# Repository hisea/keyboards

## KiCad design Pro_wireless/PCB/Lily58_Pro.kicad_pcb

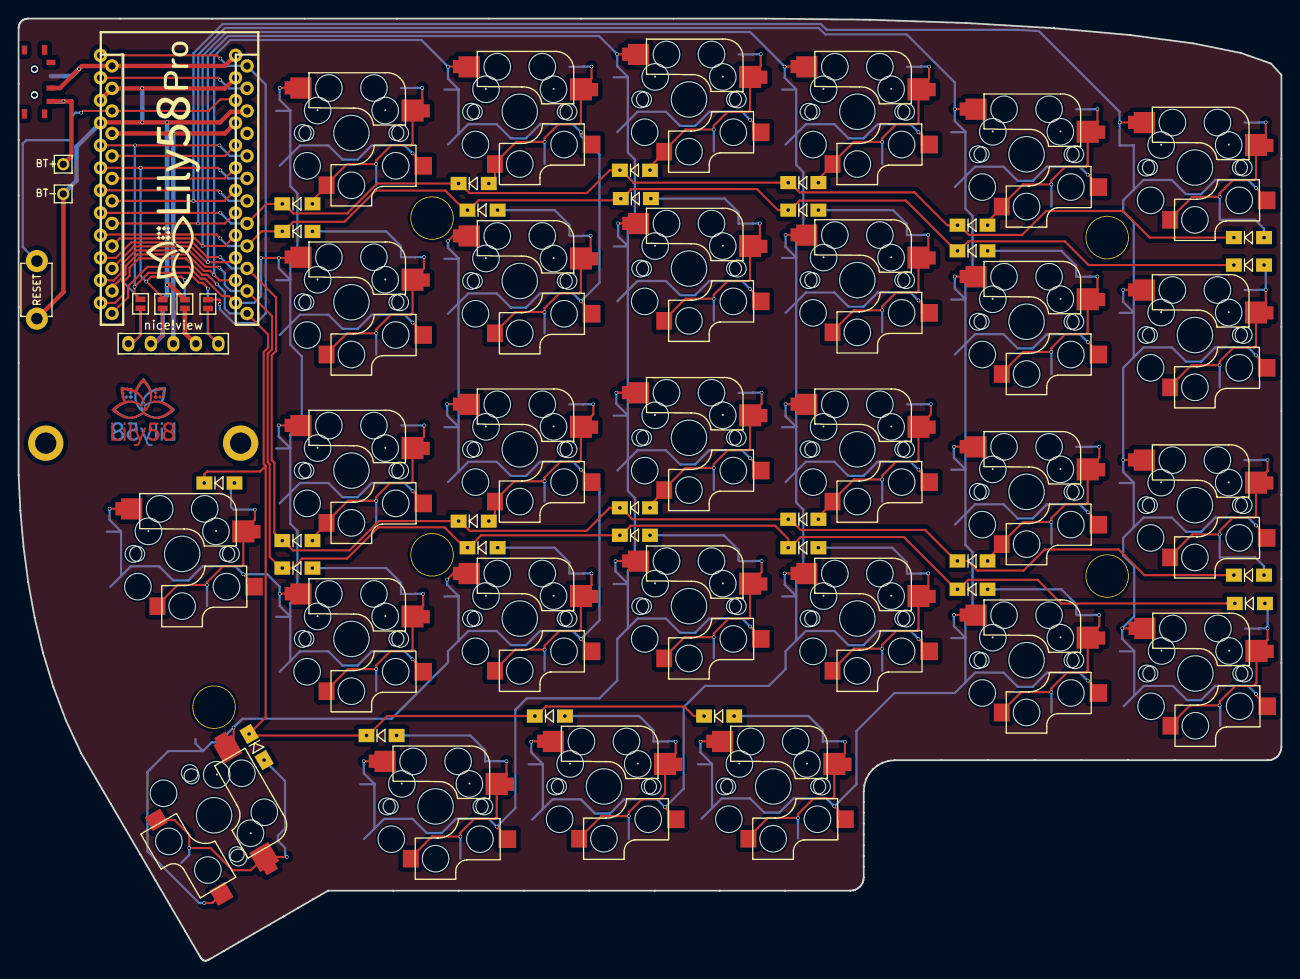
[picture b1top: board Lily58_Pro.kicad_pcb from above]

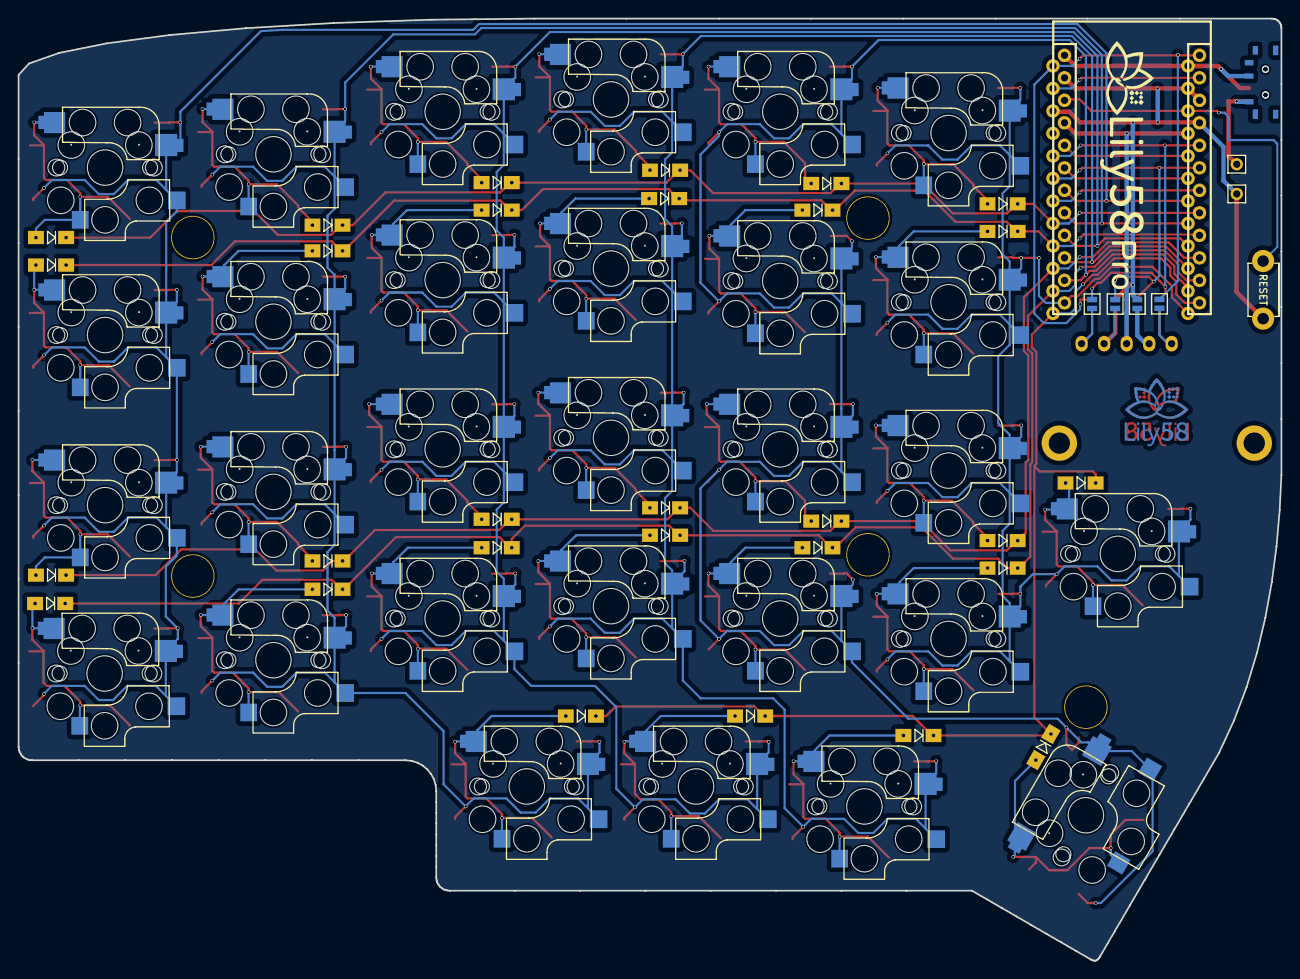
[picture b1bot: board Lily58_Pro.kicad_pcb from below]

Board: 2 copper layers, 142.5 x 106.3 mm, 80 parts (5 on the bottom side), 23 nets.

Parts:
BT+: BATT+; 1pin_conn
BT-: BATT_GND; 1pin_conn
D1, D2, D3, D4, D5, D6, D7, D8, D9, D10, D11, D12, D13, D14, D15, D16, D17, D18, D19, D20, D21, D22, D23, D24, D25, D26, D27, D28, D29: D; Diode_SOD123
Display1: nice!view; nice_view_1side
JP1, JP2, JP3, JP4, JP5, JP6, JP7, JP8: Jumper
PWSW1, PWSW2: SW_SPDT_312; switch-MSK-12C02-smd
RSW1: SW_RST; TACT_SWITCH_TVBP06
SW1, SW2, SW3, SW4, SW5, SW6, SW7, SW8, SW9, SW10, SW11, SW12, SW13, SW14, SW15, SW16, SW17, SW18, SW19, SW20, SW21, SW22, SW23, SW24, SW25, SW26, SW27, SW28, SW29: SW_PUSH; CherryMX_KailhLowProfile_Hotswap_edge
TH1, TH2: HOLE; M2_HOLE_PCB
TH3, TH4, TH5, TH6, TH7: HOLE; HOLE_M2_TH
U1: ProMicro; ProMicro_rev2

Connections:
BATT+: PWSW1.2 (C), PWSW2.2 (C), U1.24 (RAW)
DATA: JP1.2, JP8.2, U1.1 (TX(PD3))
GND: BT-.1, JP2.2, JP7.2, RSW1.1, U1.3 (GND), U1.4 (GND), U1.23 (GND)
unnamed: Display1.5 (CS), JP1.1, JP5.1
unnamed: Display1.4 (GND), JP2.1, JP6.1
unnamed: Display1.1 (MOSI), JP4.1, JP8.1
unnamed: Display1.2 (SCK), JP3.1, JP7.1
unnamed: BT+.1, PWSW1.1 (B), PWSW2.3 (A)
RESET: RSW1.2, U1.22 (RST)
SCL: JP3.2, JP6.2, U1.6 (SCL(PD0))
SDA: JP4.2, JP5.2, U1.5 (SDA(PD1))
VCC: Display1.3 (VCC), U1.21 (VCC)
col0: SW6.1, SW12.1, SW18.1, SW24.1, U1.18 (A1(PF6))
col1: SW5.1, SW11.1, SW17.1, SW23.1, SW29.1, U1.17 (A0(PF7))
col2: SW4.1, SW10.1, SW16.1, SW22.1, SW28.1, U1.16 (D15(PB1))
col3: SW3.1, SW9.1, SW15.1, SW21.1, SW27.1, U1.15 (D14(PB3))
col4: SW2.1, SW8.1, SW14.1, SW20.1, SW26.1, U1.14 (D16(PB2))
col5: SW1.1, SW7.1, SW13.1, SW19.1, SW25.1, U1.13 (D10(PB6))
row0: D1.1 (K), D2.1 (K), D3.1 (K), D4.1 (K), D5.1 (K), D6.1 (K), U1.8 (D5(PC6))
row1: D7.1 (K), D8.1 (K), D9.1 (K), D10.1 (K), D11.1 (K), D12.1 (K), U1.9 (D6(PD7))
row2: D13.1 (K), D14.1 (K), D15.1 (K), D16.1 (K), D17.1 (K), D18.1 (K), U1.10 (D7(PE6))
row3: D19.1 (K), D20.1 (K), D21.1 (K), D22.1 (K), D23.1 (K), D24.1 (K), U1.11 (D8(PB4))
row4: D25.1 (K), D26.1 (K), D27.1 (K), D28.1 (K), D29.1 (K), U1.12 (D9(PB5))

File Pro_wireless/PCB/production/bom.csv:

Designator,Footprint,Quantity,Value,LCSC Part #
BT+,1pin_conn,1,BATT+,
BT-,1pin_conn,1,BATT_GND,
"D1, D10, D11, D12, D13, D14, D15, D16, D17, D18, D19, D2, D20, D21, D22, D23, D24, D25, D26, D27, D28, D29, D3, D4, D5, D6, D7, D8, D9",Diode_SOD123,29,D,
Display1,nice_view_1side,1,nice!view,
"JP1, JP2, JP3, JP4, JP5, JP6, JP7, JP8",Jumper,8,~,
"PWSW1, PWSW2",switch-MSK-12C02-smd,2,SW_SPDT_312,
RSW1,TACT_SWITCH_TVBP06,1,SW_RST,
"SW1, SW10, SW11, SW12, SW13, SW14, SW15, SW16, SW17, SW18, SW19, SW2, SW20, SW21, SW22, SW23, SW24, SW25, SW26, SW27, SW28, SW29, SW3, SW4, SW5, SW6, SW7, SW8, SW9",CherryMX_KailhLowProfile_Hotswap_edge,29,SW_PUSH,
"TH1, TH2",M2_HOLE_PCB,2,HOLE,
"TH3, TH4, TH5, TH6, TH7",HOLE_M2_TH,5,HOLE,
U1,ProMicro_rev2,1,ProMicro,

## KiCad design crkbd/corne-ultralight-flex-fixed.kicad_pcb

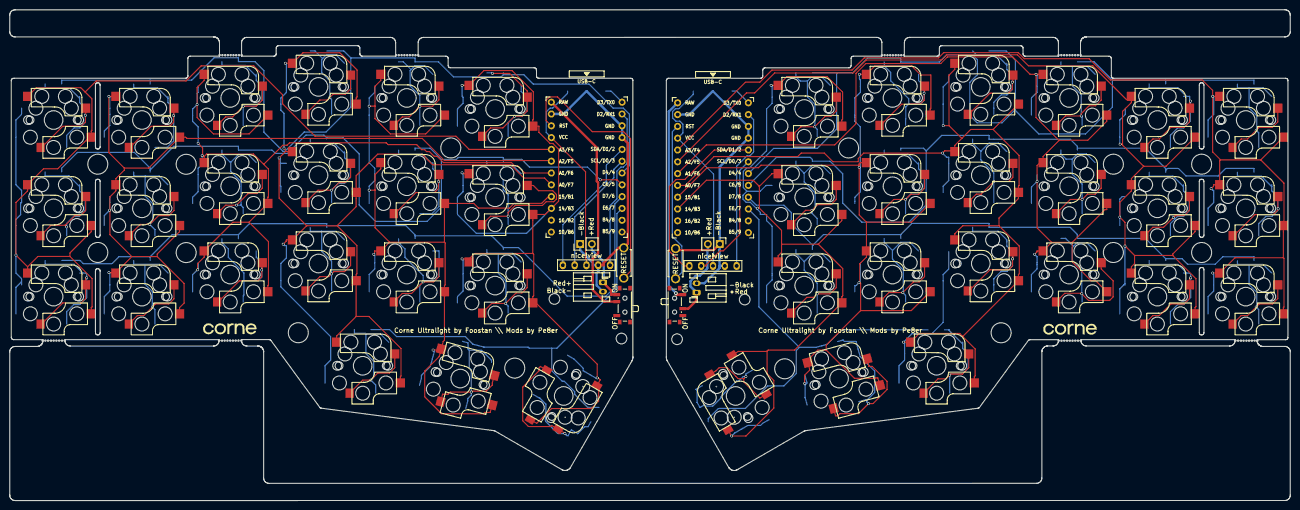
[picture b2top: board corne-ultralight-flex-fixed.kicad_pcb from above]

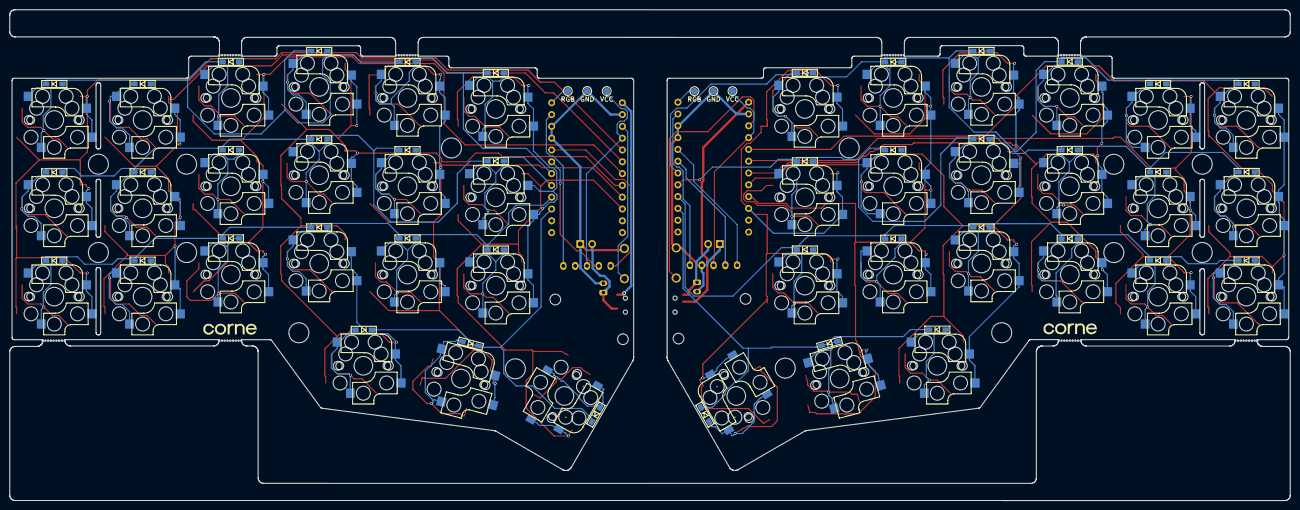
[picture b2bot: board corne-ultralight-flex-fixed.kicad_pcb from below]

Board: 2 copper layers, 275.5 x 105.6 mm, 132 parts (52 on the bottom side), 80 nets.

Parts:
BATJ1, BATJ3: Conn_01x02_Female; PinHeader_1x02_P2.54mm_Vertical
BATJ2, BATJ4: Conn_01x02_Female; JST_PH_S2B-PH-K_1x02_P2.00mm_Horizontal
D1, D2, D3, D4, D5, D6, D7, D8, D9, D10, D11, D12, D13, D14, D15, D16, D17, D18, D19, D20, D21, D22, D23, D24, D25, D26, D27, D28, D29, D30, D31, D32, D33, D34, D35, D36, D37, D38, D39, D40, D41, D42: D; D3_SMD_v2
GRAPHIC BR: LOGO; corne-logo-horizontal
GRAPHIC FR: LOGO; corne-logo-horizontal
Graphic BL: LOGO; corne-logo-horizontal
Graphic FL: LOGO; corne-logo-horizontal
HOLE1, HOLE2, HOLE8, HOLE9: Val**; thread_m2
HOLE3, HOLE4, HOLE5, HOLE6, HOLE7, HOLE10, HOLE11, HOLE12, HOLE13, HOLE14, HOLE15, HOLE16, HOLE17, HOLE18: Val**; spacer_m2
J1, J2, J3, J4, J5, J6, J7, J8: Breakaway_Tabs
J2.1, J2.2: OLED; nice_view_1side
PSW1, PSW2: SW_SPST; SW_SPDT_PCM12
RSW1, RSW2: SW_PUSH; ResetSW_1side
SW1, SW2, SW3, SW4, SW5, SW6, SW7, SW8, SW9, SW10, SW11, SW12, SW13, SW14, SW15, SW16, SW17, SW18, SW19, SW20, SW22, SW23, SW24, SW25, SW26, SW27, SW28, SW29, SW30, SW31, SW32, SW33, SW34, SW35, SW36, SW37, SW38, SW39, SW40, SW41: SW_PUSH; CherryMX_Choc_Hotswap
SW21, SW42: SW_PUSH; CherryMX_Choc_Hotswap_1.5u
TP1, TP4: RGB; TestPoint_Pad_D1.5mm
TP2, TP5: VCC; TestPoint_Pad_D1.5mm
TP3, TP6: GND; TestPoint_Pad_D1.5mm
U1, U2: ProMicro; ProMicro_v3

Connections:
+BATT: PSW1.2 (B), U1.24 (RAW)
+BATTA: PSW2.1 (A), U2.24 (RAW)
CS: J2.1.5, U1.2 (RX1/D2)
CS_r: J2.2.5, U2.2 (RX1/D2)
GND: BATJ1.1, BATJ2.2, J2.1.4, RSW1.2, TP3.1, U1.3 (GND), U1.4 (GND), U1.23 (GND)
GNDA: BATJ3.1, BATJ4.2, J2.2.4, RSW2.2, TP6.1, U2.3 (GND), U2.4 (GND), U2.23 (GND)
unnamed: BATJ1.2, BATJ2.1, PSW1.3 (C)
unnamed: BATJ3.2, BATJ4.1, PSW2.2 (B)
unnamed: D1.2 (A), SW1.2
unnamed: D2.2 (A), SW2.2
unnamed: D3.2 (A), SW3.2
unnamed: D4.2 (A), SW4.2
unnamed: D5.2 (A), SW5.2
unnamed: D6.2 (A), SW6.2
unnamed: D7.2 (A), SW7.2
unnamed: D8.2 (A), SW8.2
unnamed: D9.2 (A), SW9.2
unnamed: D10.2 (A), SW10.2
unnamed: D11.2 (A), SW11.2
unnamed: D12.2 (A), SW12.2
unnamed: D13.2 (A), SW13.2
unnamed: D14.2 (A), SW14.2
unnamed: D15.2 (A), SW15.2
unnamed: D16.2 (A), SW16.2
unnamed: D17.2 (A), SW17.2
unnamed: D18.2 (A), SW18.2
unnamed: D19.2 (A), SW19.2
unnamed: D20.2 (A), SW20.2
unnamed: D21.2 (A), SW21.2
unnamed: D22.2 (A), SW22.2
unnamed: D23.2 (A), SW23.2
unnamed: D24.2 (A), SW24.2
unnamed: D25.2 (A), SW25.2
unnamed: D26.2 (A), SW26.2
unnamed: D27.2 (A), SW27.2
unnamed: D28.2 (A), SW28.2
unnamed: D29.2 (A), SW29.2
unnamed: D30.2 (A), SW30.2
unnamed: D31.2 (A), SW31.2
unnamed: D32.2 (A), SW32.2
unnamed: D33.2 (A), SW33.2
unnamed: D34.2 (A), SW34.2
unnamed: D35.2 (A), SW35.2
unnamed: D36.2 (A), SW36.2
unnamed: D37.2 (A), SW37.2
unnamed: D38.2 (A), SW38.2
unnamed: D39.2 (A), SW39.2
unnamed: D40.2 (A), SW40.2
unnamed: D41.2 (A), SW41.2
unnamed: D42.2 (A), SW42.2
RGB: TP1.1, U1.1 (TX0/D3)
RGB_r: TP4.1, U2.1 (TX0/D3)
SCL: J2.1.2, U1.6 (3/D0/SCL)
SCL_r: J2.2.2, U2.6 (3/D0/SCL)
SDA: J2.1.1, U1.5 (2/D1/SDA)
SDA_r: J2.2.1, U2.5 (2/D1/SDA)
VCC: J2.1.3, TP2.1, U1.21 (VCC)
VDD: J2.2.3, TP5.1, U2.21 (VCC)
col0: SW1.1, SW7.1, SW13.1, U1.20 (F4/A3)
col0_r: SW22.1, SW28.1, SW34.1, U2.20 (F4/A3)
col1: SW2.1, SW8.1, SW14.1, U1.19 (F5/A2)
col1_r: SW23.1, SW29.1, SW35.1, U2.19 (F5/A2)
col2: SW3.1, SW9.1, SW15.1, U1.18 (F6/A1)
col2_r: SW24.1, SW30.1, SW36.1, U2.18 (F6/A1)
col3: SW4.1, SW10.1, SW16.1, SW19.1, U1.17 (F7/A0)
col3_r: SW25.1, SW31.1, SW37.1, SW40.1, U2.17 (F7/A0)
col4: SW5.1, SW11.1, SW17.1, SW20.1, U1.16 (B1/15)
col4_r: SW26.1, SW32.1, SW38.1, SW41.1, U2.16 (B1/15)
col5: SW6.1, SW12.1, SW18.1, SW21.1, U1.15 (B3/14)
col5_r: SW27.1, SW33.1, SW39.1, SW42.1, U2.15 (B3/14)
reset: RSW1.1, U1.22 (RST)
reset_r: RSW2.1, U2.22 (RST)
row0: D1.1 (K), D2.1 (K), D3.1 (K), D4.1 (K), D5.1 (K), D6.1 (K), U1.7 (4/D4)
row0_r: D22.1 (K), D23.1 (K), D24.1 (K), D25.1 (K), D26.1 (K), D27.1 (K), U2.7 (4/D4)
row1: D7.1 (K), D8.1 (K), D9.1 (K), D10.1 (K), D11.1 (K), D12.1 (K), U1.8 (5/C6)
row1_r: D28.1 (K), D29.1 (K), D30.1 (K), D31.1 (K), D32.1 (K), D33.1 (K), U2.8 (5/C6)
row2: D13.1 (K), D14.1 (K), D15.1 (K), D16.1 (K), D17.1 (K), D18.1 (K), U1.9 (6/D7)
row2_r: D34.1 (K), D35.1 (K), D36.1 (K), D37.1 (K), D38.1 (K), D39.1 (K), U2.9 (6/D7)
row3: D19.1 (K), D20.1 (K), D21.1 (K), U1.10 (7/E6)
row3_r: D40.1 (K), D41.1 (K), D42.1 (K), U2.10 (7/E6)

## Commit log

2024-09-01 init
2024-12-01 Add lily 58 wireless.
